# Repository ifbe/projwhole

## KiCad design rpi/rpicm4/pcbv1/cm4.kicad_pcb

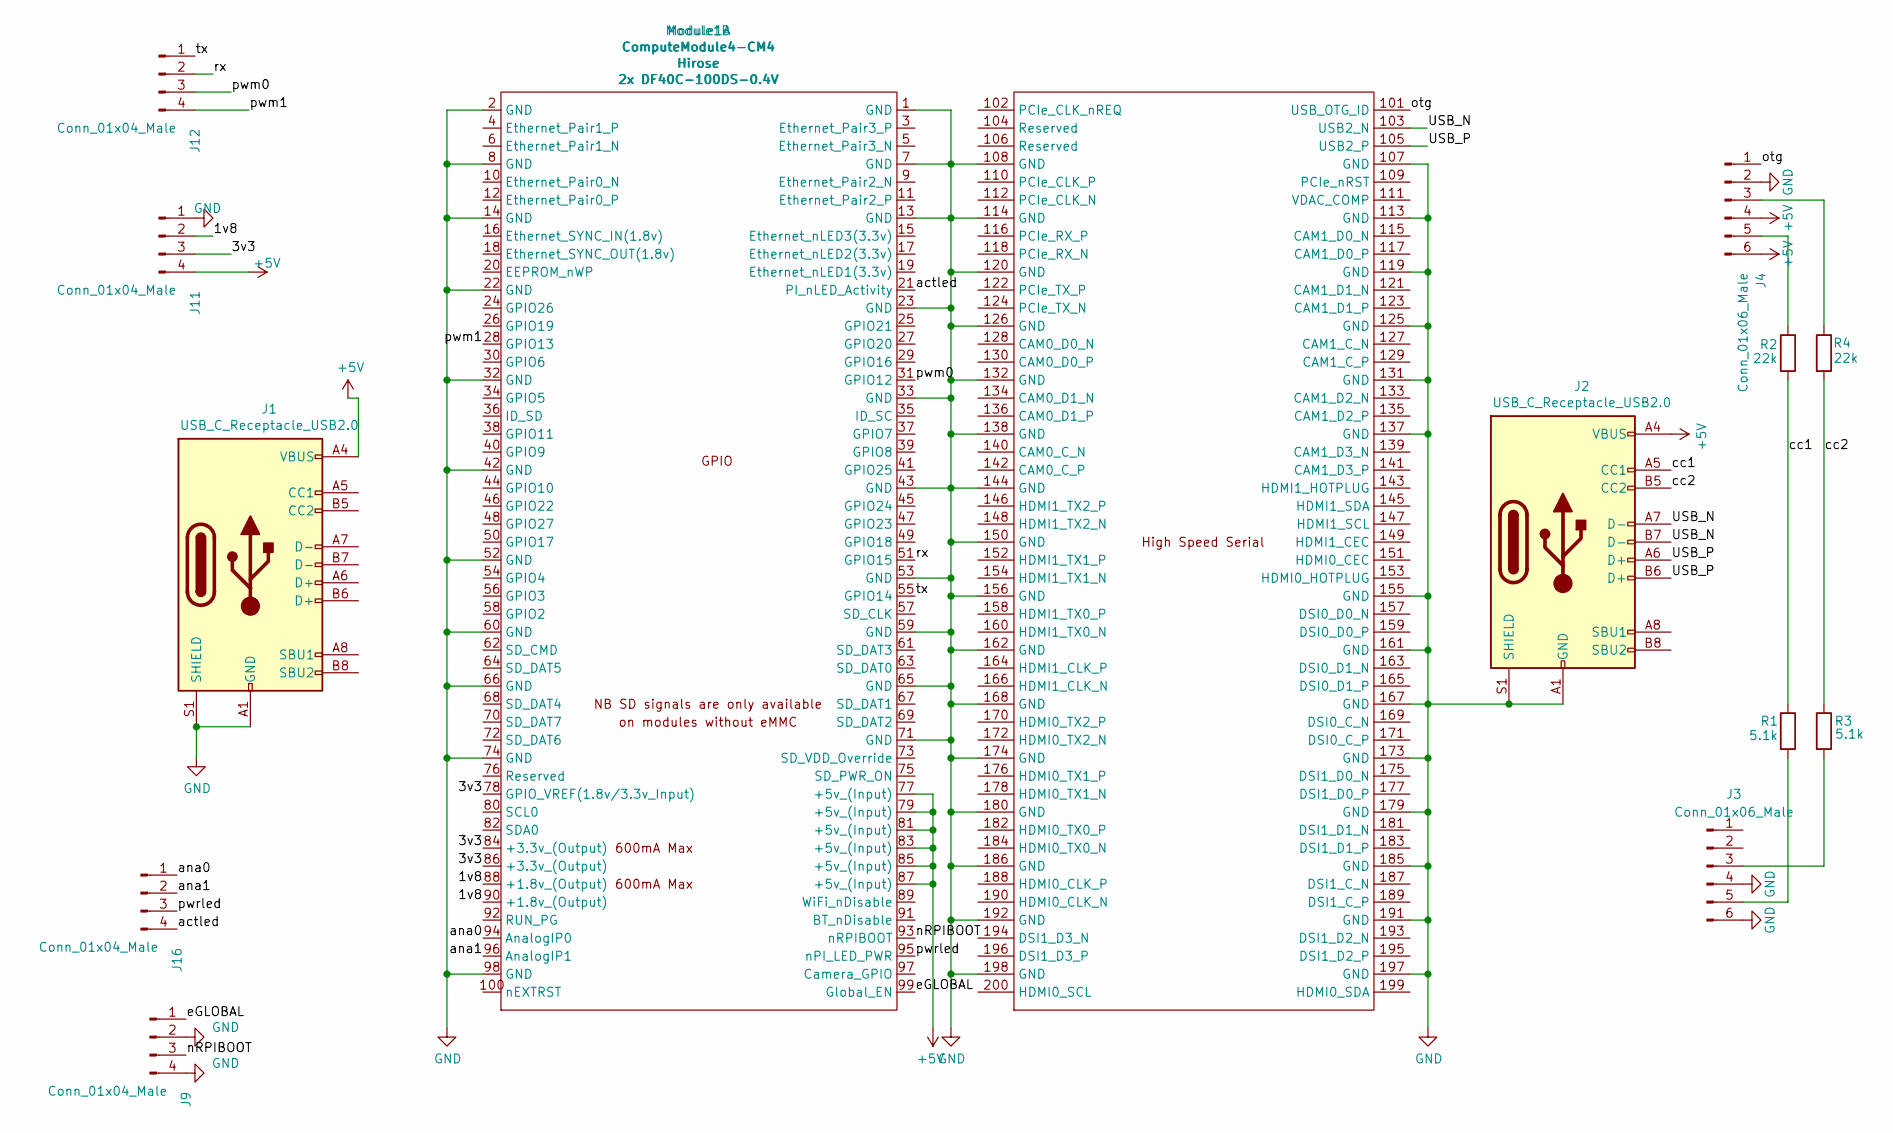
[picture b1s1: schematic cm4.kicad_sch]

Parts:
J1, J2: USB_C_Receptacle_USB2.0; USB_C_Receptacle_XKB_U262-16XN-4BVC11
J3, J4: Conn_01x06_Male; PinHeader_1x06_P2.54mm_Vertical
J9, J11, J12, J16: Conn_01x04_Male; PinHeader_1x04_P2.54mm_Vertical
Module1: ComputeModule4-CM4; Raspberry-Pi-4-Compute-Module
R1, R3: 5.1k; R_Axial_DIN0207_L6.3mm_D2.5mm_P10.16mm_Horizontal
R2, R4: 22k; R_Axial_DIN0207_L6.3mm_D2.5mm_P10.16mm_Horizontal

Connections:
+5V: J1.A4 (VBUS), J1.A9 (VBUS), J1.B4 (VBUS), J1.B9 (VBUS), J2.A4 (VBUS), J2.A9 (VBUS), J2.B4 (VBUS), J2.B9 (VBUS), J4.4, J4.6, J11.4, Module1.77 (+5v_(Input)), Module1.79 (+5v_(Input)), Module1.81 (+5v_(Input)), Module1.83 (+5v_(Input)), Module1.85 (+5v_(Input)), Module1.87 (+5v_(Input))
/1v8: J11.2, Module1.88 (+1.8v_(Output)), Module1.90 (+1.8v_(Output))
/3v3: J11.3, Module1.78 (GPIO_VREF(1.8v/3.3v_Input)), Module1.84 (+3.3v_(Output)), Module1.86 (+3.3v_(Output))
/USB_N: J2.A7 (D-), J2.B7 (D-), Module1.103 (USB2_N)
/USB_P: J2.A6 (D+), J2.B6 (D+), Module1.105 (USB2_P)
/actled: J16.4, Module1.21 (PI_nLED_Activity)
/ana0: J16.1, Module1.94 (AnalogIP0)
/ana1: J16.2, Module1.96 (AnalogIP1)
/cc1: J2.A5 (CC1), R1.1, R2.2
/cc2: J2.B5 (CC2), R3.1, R4.2
/eGLOBAL: J9.1, Module1.99 (Global_EN)
/nRPIBOOT: J9.3, Module1.93 (nRPIBOOT)
/otg: J4.1, Module1.101 (USB_OTG_ID)
/pwm0: J12.3, Module1.31 (GPIO12)
/pwm1: J12.4, Module1.28 (GPIO13)
/pwrled: J16.3, Module1.95 (nPI_LED_PWR)
/rx: J12.2, Module1.51 (GPIO15)
/tx: J12.1, Module1.55 (GPIO14)
GND: J1.A1 (GND), J1.A12 (GND), J1.B1 (GND), J1.B12 (GND), J1.S1 (SHIELD), J2.A1 (GND), J2.A12 (GND), J2.B1 (GND), J2.B12 (GND), J2.S1 (SHIELD), J3.4, J3.6, J4.2, J9.2, J9.4, J11.1, Module1.1 (GND), Module1.2 (GND), Module1.7 (GND), Module1.8 (GND), Module1.13 (GND), Module1.14 (GND), Module1.22 (GND), Module1.23 (GND), Module1.32 (GND), Module1.33 (GND), Module1.42 (GND), Module1.43 (GND), Module1.52 (GND), Module1.53 (GND), Module1.59 (GND), Module1.60 (GND), Module1.65 (GND), Module1.66 (GND), Module1.71 (GND), Module1.74 (GND), Module1.98 (GND), Module1.107 (GND), Module1.108 (GND), Module1.113 (GND), Module1.114 (GND), Module1.119 (GND), Module1.120 (GND), Module1.125 (GND), Module1.126 (GND), Module1.131 (GND), Module1.132 (GND), Module1.137 (GND), Module1.138 (GND), Module1.144 (GND), Module1.150 (GND), Module1.155 (GND), Module1.156 (GND), Module1.161 (GND), Module1.162 (GND), Module1.167 (GND), Module1.168 (GND), Module1.173 (GND), Module1.174 (GND), Module1.179 (GND), Module1.180 (GND), Module1.185 (GND), Module1.186 (GND), Module1.191 (GND), Module1.192 (GND), Module1.197 (GND), Module1.198 (GND)
unnamed: J3.5, R1.2
unnamed: J4.5, R2.1
unnamed: J3.3, R3.2
unnamed: J4.3, R4.1

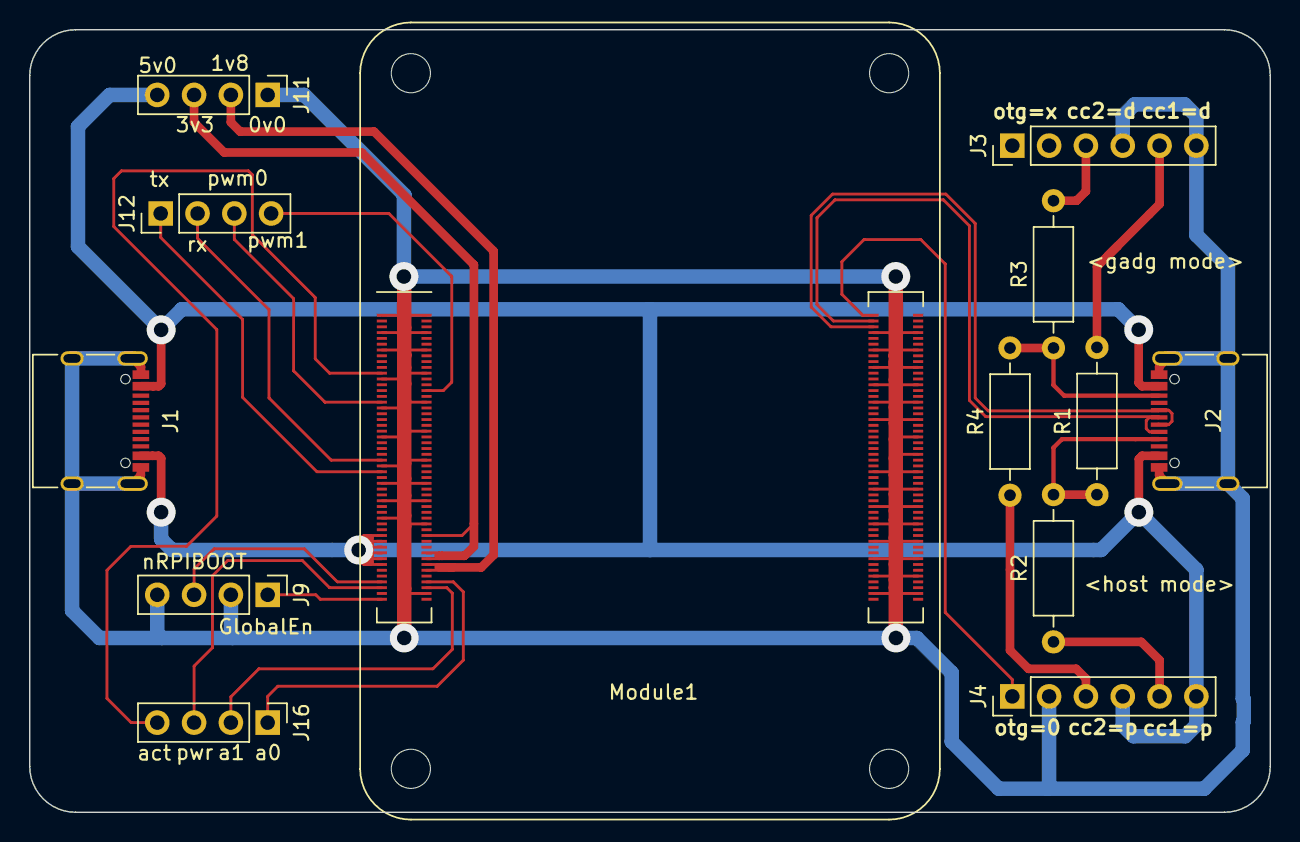
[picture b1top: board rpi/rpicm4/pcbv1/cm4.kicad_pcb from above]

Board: 2 copper layers, 85.6 x 54.0 mm, 13 parts (0 on the bottom side), 23 nets.

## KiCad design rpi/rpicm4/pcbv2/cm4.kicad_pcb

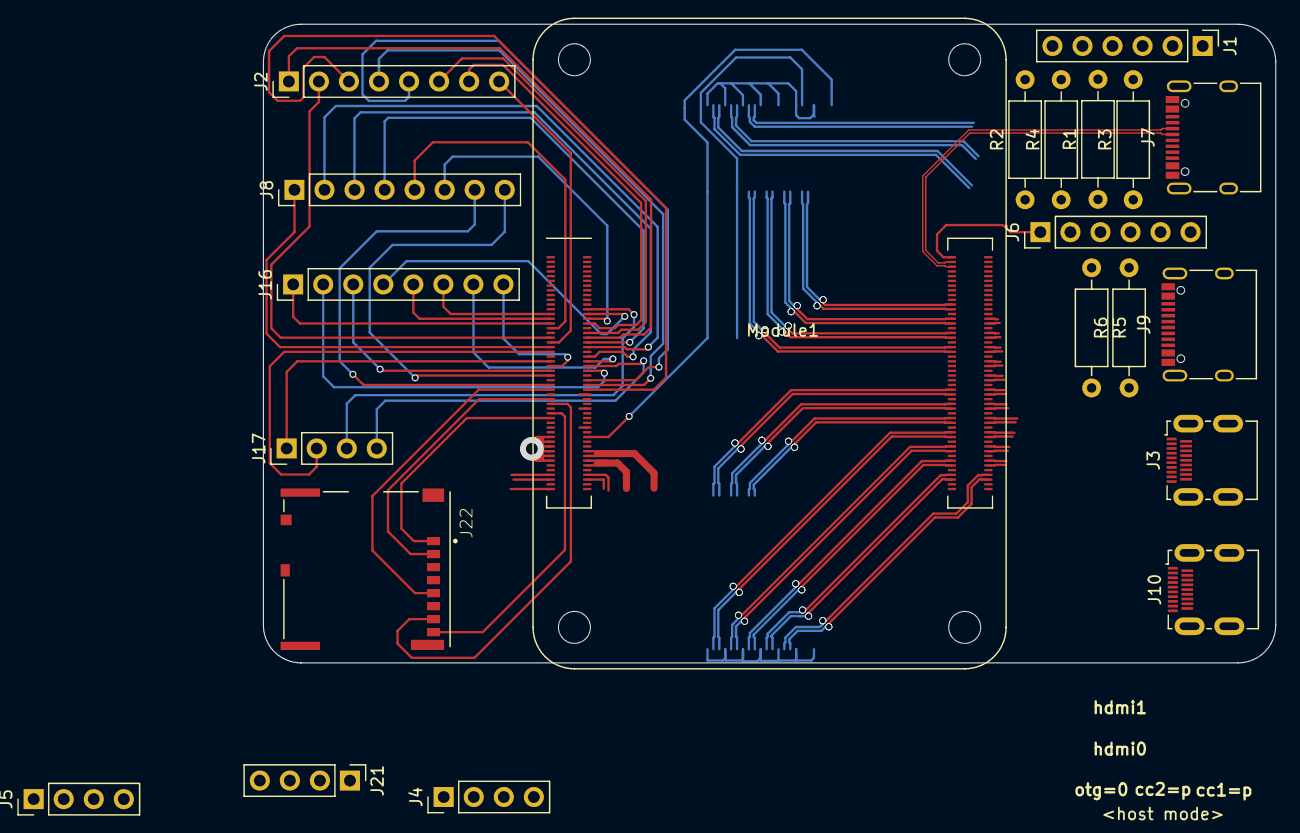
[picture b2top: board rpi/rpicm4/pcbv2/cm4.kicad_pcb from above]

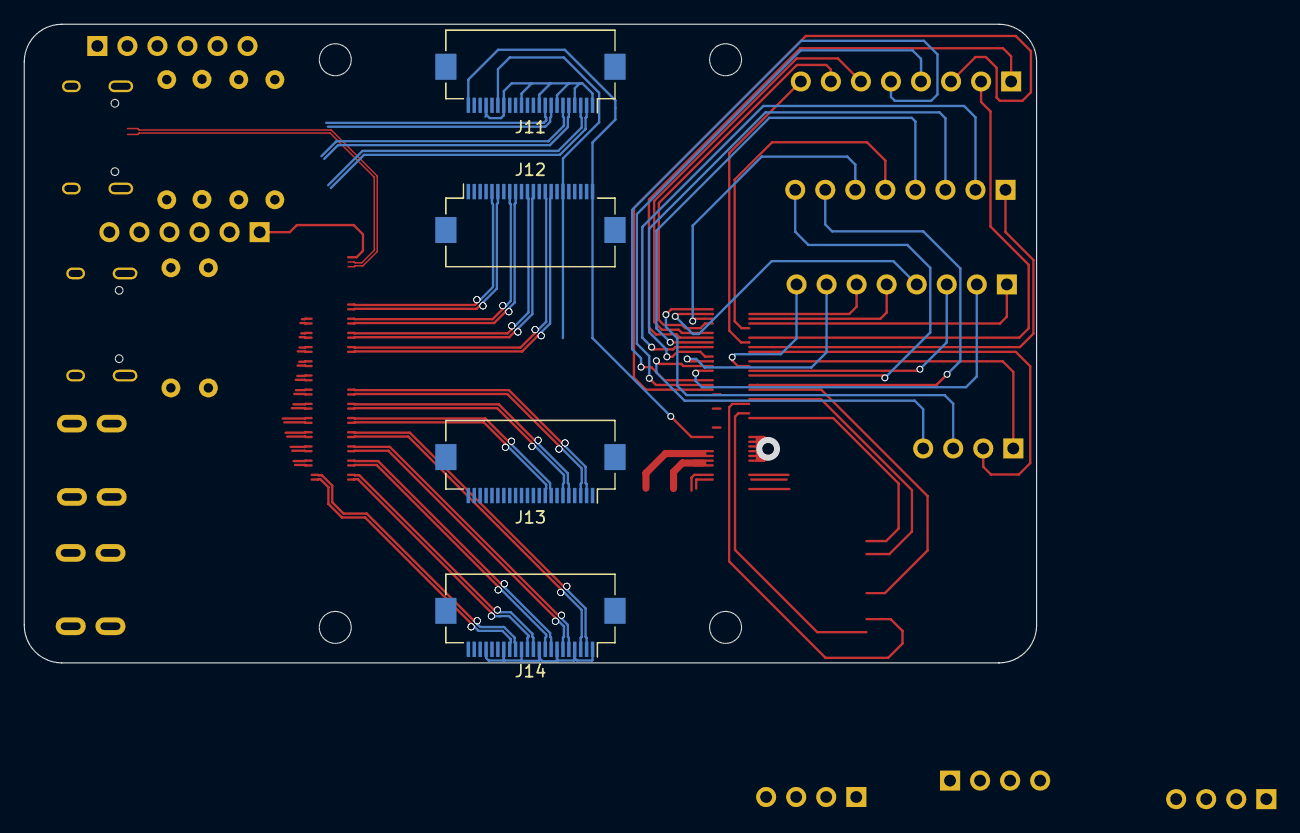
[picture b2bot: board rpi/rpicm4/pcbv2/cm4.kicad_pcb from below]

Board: 2 copper layers, 85.6 x 54.0 mm, 25 parts (4 on the bottom side), 114 nets.

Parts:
J1, J6: Conn_01x06_Male; PinHeader_1x06_P2.54mm_Vertical
J2, J8, J16: Conn_01x08_Male; PinHeader_1x08_P2.54mm_Vertical
J3, J10: HDMI_A_1.4; HDMI_Micro-D_Molex_46765-1x01
J4, J5, J17, J21: Conn_01x04_Male; PinHeader_1x04_P2.54mm_Vertical
J7, J9: USB_C_Receptacle_USB2.0; USB_C_Receptacle_XKB_U262-16XN-4BVC11
J11, J12, J13, J14: Conn_01x22_Female; Hirose_FH12-22S-0.5SH_1x22-1MP_P0.50mm_Horizontal
J22: Micro_SD_Card_Det; SDCARD_MOLEX_503398-1892
Module1: ComputeModule4-CM4; Raspberry-Pi-4-Compute-Module
R1, R3: 22k; R_Axial_DIN0207_L6.3mm_D2.5mm_P10.16mm_Horizontal
R2, R4, R5, R6: 5.1k; R_Axial_DIN0207_L6.3mm_D2.5mm_P10.16mm_Horizontal

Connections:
+1V8: J4.2, Module1.88 (+1.8v_(Output)), Module1.90 (+1.8v_(Output))
+3V3: J4.3, J11.22, J12.22, J13.22, J14.22, Module1.78 (GPIO_VREF(1.8v/3.3v_Input)), Module1.84 (+3.3v_(Output)), Module1.86 (+3.3v_(Output))
+5V: J3.18 (+5V), J4.4, J6.4, J6.6, J7.A4 (VBUS), J7.A9 (VBUS), J7.B4 (VBUS), J7.B9 (VBUS), J9.A4 (VBUS), J9.A9 (VBUS), J9.B4 (VBUS), J9.B9 (VBUS), J10.18 (+5V), Module1.77 (+5v_(Input)), Module1.79 (+5v_(Input)), Module1.81 (+5v_(Input)), Module1.83 (+5v_(Input)), Module1.85 (+5v_(Input)), Module1.87 (+5v_(Input))
GND: J1.4, J1.6, J3.2 (D2S), J3.5 (D1S), J3.8 (D0S), J3.11 (CKS), J3.17 (GND), J4.1, J6.2, J7.A1 (GND), J7.A12 (GND), J7.B1 (GND), J7.B12 (GND), J7.S1 (SHIELD), J9.A1 (GND), J9.A12 (GND), J9.B1 (GND), J9.B12 (GND), J9.S1 (SHIELD), J10.2 (D2S), J10.5 (D1S), J10.8 (D0S), J10.11 (CKS), J10.17 (GND), J11.1, J11.4, J11.7, J11.10, J11.13, J11.16, J11.19, J12.1, J12.4, J12.7, J12.10, J12.13, J12.16, J12.19, J13.1, J13.4, J13.7, J13.10, J13.13, J13.16, J13.19, J14.1, J14.4, J14.7, J14.10, J14.13, J14.16, J14.19, Module1.1 (GND), Module1.2 (GND), Module1.7 (GND), Module1.8 (GND), Module1.13 (GND), Module1.14 (GND), Module1.22 (GND), Module1.23 (GND), Module1.32 (GND), Module1.33 (GND), Module1.42 (GND), Module1.43 (GND), Module1.52 (GND), Module1.53 (GND), Module1.59 (GND), Module1.60 (GND), Module1.65 (GND), Module1.66 (GND), Module1.71 (GND), Module1.74 (GND), Module1.98 (GND), Module1.107 (GND), Module1.108 (GND), Module1.113 (GND), Module1.114 (GND), Module1.119 (GND), Module1.120 (GND), Module1.125 (GND), Module1.126 (GND), Module1.131 (GND), Module1.132 (GND), Module1.137 (GND), Module1.138 (GND), Module1.144 (GND), Module1.150 (GND), Module1.155 (GND), Module1.156 (GND), Module1.161 (GND), Module1.162 (GND), Module1.167 (GND), Module1.168 (GND), Module1.173 (GND), Module1.174 (GND), Module1.179 (GND), Module1.180 (GND), Module1.185 (GND), Module1.186 (GND), Module1.191 (GND), Module1.192 (GND), Module1.197 (GND), Module1.198 (GND), R5.2, R6.2
unnamed: J1.3, R4.2
unnamed: J1.5, R2.2
unnamed: J6.3, R3.1
unnamed: J6.5, R1.1
unnamed: J9.A5 (CC1), R6.1
unnamed: J9.B5 (CC2), R5.1
SD_CLK: J22.5 (CLK), Module1.57 (SD_CLK)
SD_CMD: J22.3 (CMD), Module1.62 (SD_CMD)
SD_DAT0: J22.7 (DAT0), Module1.63 (SD_DAT0)
SD_DAT1: J22.8 (DAT1), Module1.67 (SD_DAT1)
SD_DAT2: J22.1 (DAT2), Module1.69 (SD_DAT2)
SD_DAT3: J22.2 (DAT3/CD), Module1.61 (SD_DAT3)
USB_N: J7.A7 (D-), J7.B7 (D-), Module1.103 (USB2_N)
USB_P: J7.A6 (D+), J7.B6 (D+), Module1.105 (USB2_P)
actled: J5.3, Module1.21 (PI_nLED_Activity)
analog0: J5.1, Module1.94 (AnalogIP0)
analog1: J5.2, Module1.96 (AnalogIP1)
cam0_c_N: J11.8, Module1.140 (CAM0_C_N)
cam0_c_P: J11.9, Module1.142 (CAM0_C_P)
cam0_d0_N: J11.2, Module1.128 (CAM0_D0_N)
cam0_d0_P: J11.3, Module1.130 (CAM0_D0_P)
cam0_d1_N: J11.5, Module1.134 (CAM0_D1_N)
cam0_d1_P: J11.6, Module1.136 (CAM0_D1_P)
cam1_c_N: J12.8, Module1.127 (CAM1_C_N)
cam1_c_P: J12.9, Module1.129 (CAM1_C_P)
cam1_d1_N: J12.5, Module1.121 (CAM1_D1_N)
cam1_d1_P: J12.6, Module1.123 (CAM1_D1_P)
cam1_d2_N: J12.11, Module1.133 (CAM1_D2_N)
cam1_d2_P: J12.12, Module1.135 (CAM1_D2_P)
cam1_d3_N: J12.14, Module1.139 (CAM1_D3_N)
cam1_d3_P: J12.15, Module1.141 (CAM1_D3_P)
cam_gpio: J11.17, J12.17, Module1.97 (Camera_GPIO)
cc1: J7.A5 (CC1), R1.2, R2.1
cc2: J7.B5 (CC2), R3.2, R4.1
dsi0_c_N: J13.8, Module1.169 (DSI0_C_N)
dsi0_c_P: J13.9, Module1.171 (DSI0_C_P)
dsi0_d0_N: J13.2, Module1.157 (DSI0_D0_N)
dsi0_d0_P: J13.3, Module1.159 (DSI0_D0_P)
dsi0_d1_N: J13.5, Module1.163 (DSI0_D1_N)
dsi0_d1_P: J13.6, Module1.165 (DSI0_D1_P)
dsi1_c_N: J14.8, Module1.187 (DSI1_C_N)
dsi1_c_P: J14.9, Module1.189 (DSI1_C_P)
dsi1_d0_N: J14.2, Module1.175 (DSI1_D0_N)
dsi1_d0_P: J14.3, Module1.177 (DSI1_D0_P)
dsi1_d1_N: J14.5, Module1.181 (DSI1_D1_N)
dsi1_d1_P: J14.6, Module1.183 (DSI1_D1_P)
dsi1_d2_N: J14.11, Module1.193 (DSI1_D2_N)
dsi1_d2_P: J14.12, Module1.195 (DSI1_D2_P)
dsi1_d3_N: J14.14, Module1.194 (DSI1_D3_N)
dsi1_d3_P: J14.15, Module1.196 (DSI1_D3_P)
eGLOBAL: J21.3, Module1.99 (Global_EN)
gpio0: J2.1, Module1.36 (ID_SD)
gpio1: J2.2, Module1.35 (ID_SC)
gpio2: J2.3, Module1.58 (GPIO2)
gpio3: J2.4, Module1.56 (GPIO3)
gpio4: J2.5, Module1.54 (GPIO4)
gpio5: J2.6, Module1.34 (GPIO5)
gpio6: J2.7, Module1.30 (GPIO6)
gpio7: J2.8, Module1.37 (GPIO7)
gpio8: J8.1, Module1.39 (GPIO8)
gpio9: J8.2, Module1.40 (GPIO9)
gpio10: J8.3, Module1.44 (GPIO10)
gpio11: J8.4, Module1.38 (GPIO11)
gpio12: J8.5, Module1.31 (GPIO12)
gpio13: J8.6, Module1.28 (GPIO13)
gpio14: J8.7, Module1.55 (GPIO14)
gpio15: J8.8, Module1.51 (GPIO15)
gpio16: J16.1, Module1.29 (GPIO16)
gpio17: J16.2, Module1.50 (GPIO17)
gpio18: J16.3, Module1.49 (GPIO18)
gpio19: J16.4, Module1.26 (GPIO19)
gpio20: J16.5, Module1.27 (GPIO20)
gpio21: J16.6, Module1.25 (GPIO21)
gpio22: J16.7, Module1.46 (GPIO22)
gpio23: J16.8, Module1.47 (GPIO23)
gpio24: J17.1, Module1.45 (GPIO24)
gpio25: J17.2, Module1.41 (GPIO25)
gpio26: J17.3, Module1.24 (GPIO26)
gpio27: J17.4, Module1.48 (GPIO27)
hdmi0_cec: J10.13 (CEC), Module1.151 (HDMI0_CEC)
hdmi0_clk_N: J10.12 (CK-), Module1.190 (HDMI0_CLK_N)
hdmi0_clk_P: J10.10 (CK+), Module1.188 (HDMI0_CLK_P)
hdmi0_plug: J10.19 (HPD/HEAC-), Module1.153 (HDMI0_HOTPLUG)
hdmi0_scl: J10.15 (SCL), Module1.200 (HDMI0_SCL)
hdmi0_sda: J10.16 (SDA), Module1.199 (HDMI0_SDA)
hdmi0_tx0_N: J10.9 (D0-), Module1.184 (HDMI0_TX0_N)
hdmi0_tx0_P: J10.7 (D0+), Module1.182 (HDMI0_TX0_P)
hdmi0_tx1_N: J10.6 (D1-), Module1.178 (HDMI0_TX1_N)
hdmi0_tx1_P: J10.4 (D1+), Module1.176 (HDMI0_TX1_P)
hdmi0_tx2_N: J10.3 (D2-), Module1.172 (HDMI0_TX2_N)
hdmi0_tx2_P: J10.1 (D2+), Module1.170 (HDMI0_TX2_P)
hdmi1_cec: J3.13 (CEC), Module1.149 (HDMI1_CEC)
hdmi1_clk_N: J3.12 (CK-), Module1.166 (HDMI1_CLK_N)
hdmi1_clk_P: J3.10 (CK+), Module1.164 (HDMI1_CLK_P)
hdmi1_plug: J3.19 (HPD/HEAC-), Module1.143 (HDMI1_HOTPLUG)
hdmi1_scl: J3.15 (SCL), Module1.147 (HDMI1_SCL)
hdmi1_sda: J3.16 (SDA), Module1.145 (HDMI1_SDA)
hdmi1_tx0_N: J3.9 (D0-), Module1.160 (HDMI1_TX0_N)
hdmi1_tx0_P: J3.7 (D0+), Module1.158 (HDMI1_TX0_P)
hdmi1_tx1_N: J3.6 (D1-), Module1.154 (HDMI1_TX1_N)
hdmi1_tx1_P: J3.4 (D1+), Module1.152 (HDMI1_TX1_P)
hdmi1_tx2_N: J3.3 (D2-), Module1.148 (HDMI1_TX2_N)
hdmi1_tx2_P: J3.1 (D2+), Module1.146 (HDMI1_TX2_P)
nRPIBOOT: J21.4, Module1.93 (nRPIBOOT)
otg: J6.1, Module1.101 (USB_OTG_ID)
pwrled: J5.4, Module1.95 (nPI_LED_PWR)
scl0: J12.20, J14.20, Module1.80 (SCL0)
scl1: J11.20, J13.20
sda0: J12.21, J14.21, Module1.82 (SDA0)
sda1: J11.21, J13.21
